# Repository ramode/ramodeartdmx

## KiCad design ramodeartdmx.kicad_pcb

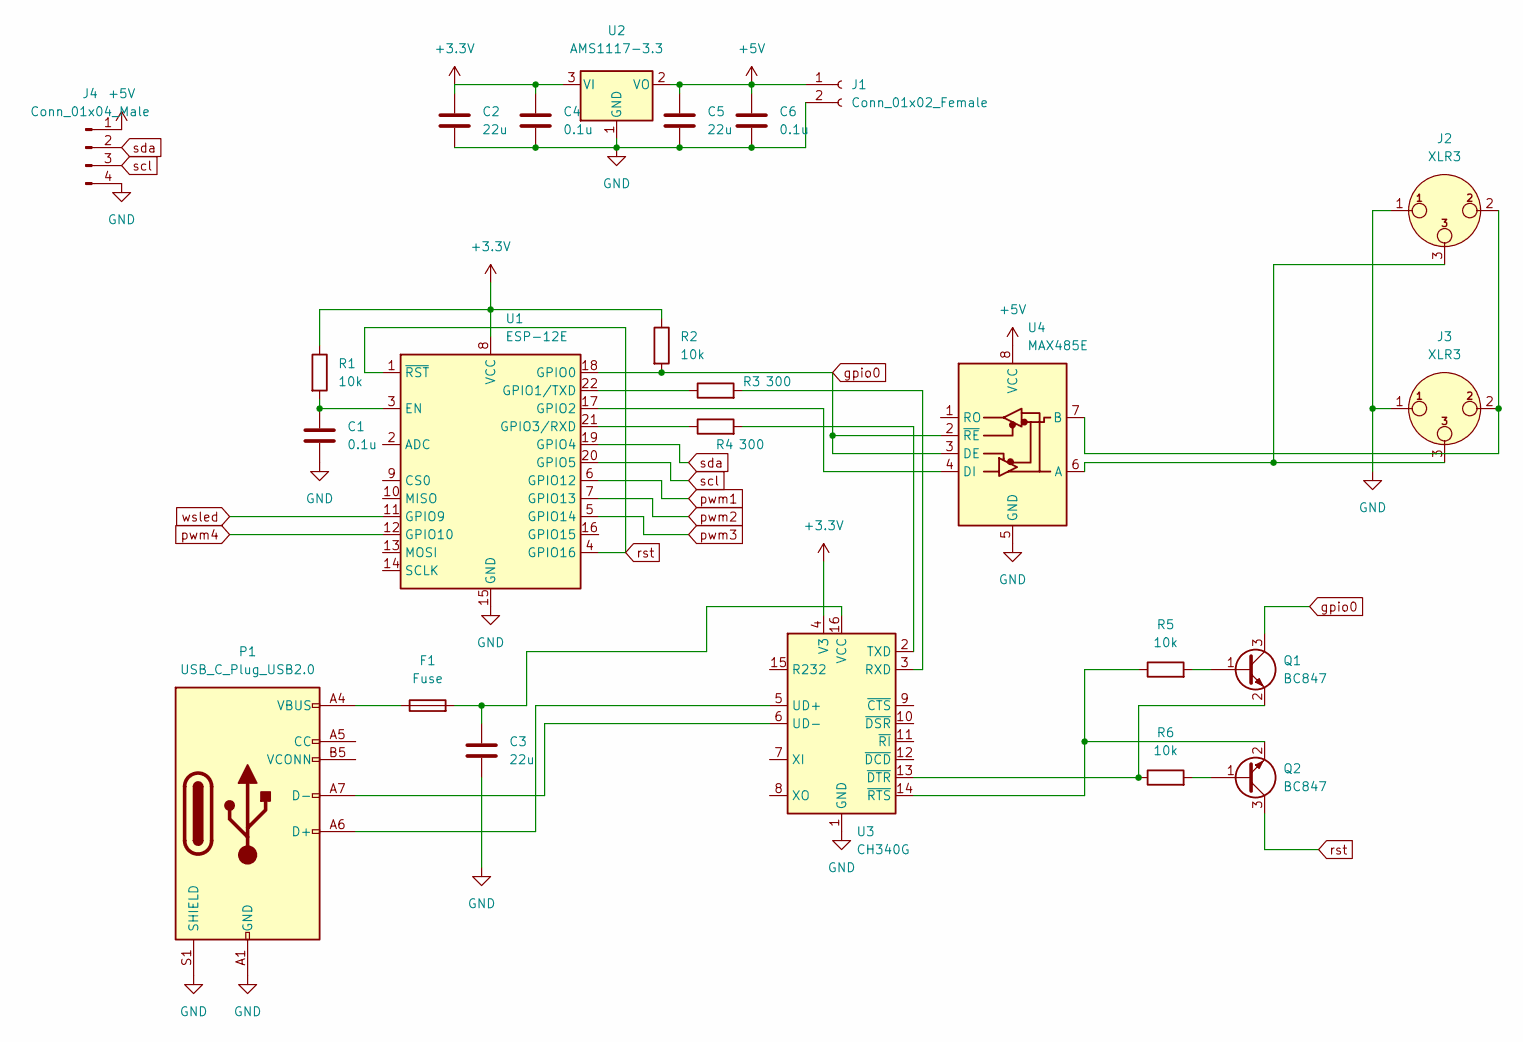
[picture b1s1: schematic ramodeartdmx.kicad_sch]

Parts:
C1, C4, C6: 0.1u; C_0805_2012Metric_Pad1.18x1.45mm_HandSolder
C2, C3, C5: 22u; C_0805_2012Metric_Pad1.18x1.45mm_HandSolder
F1: Fuse; Fuse_1206_3216Metric_Pad1.42x1.75mm_HandSolder
J1: Conn_01x02_Female; BarrelJack_Horizontal
J2, J3: XLR3; PinHeader_1x03_P2.54mm_Vertical
J4: Conn_01x04_Male; PinHeader_1x04_P2.54mm_Vertical
P1: USB_C_Plug_USB2.0; USB_C_Receptacle_JAE_DX07S016JA1R1500
Q1, Q2: BC847; SOT-23
R1, R2, R5, R6: 10k; R_0805_2012Metric_Pad1.20x1.40mm_HandSolder
R3, R4: 300; R_0805_2012Metric_Pad1.20x1.40mm_HandSolder
U1: ESP-12E
U2: AMS1117-3.3; SOT-223-3_TabPin2
U3: CH340G; SOIC-16_3.9x9.9mm_P1.27mm
U4: MAX485E; MSOP-8_3x3mm_P0.65mm

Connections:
+3V3: C2.1, C4.1, R1.1, R2.1, U1.8 (VCC), U2.3 (VI), U3.4 (V3)
+5V: C5.1, C6.1, J1.1, J4.1, U2.2 (VO), U4.8 (VCC)
GND: C1.2, C2.2, C3.2, C4.2, C5.2, C6.2, J1.2, J2.1, J3.1, J4.4, P1.A1 (GND), P1.A12 (GND), P1.B1 (GND), P1.B12 (GND), P1.S1 (SHIELD), U1.15 (GND), U2.1 (GND), U3.1 (GND), U4.5 (GND)
unnamed: C1.1, R1.2, U1.3 (EN)
unnamed: C3.1, F1.2, U3.16 (VCC)
unnamed: F1.1, P1.A4 (VBUS), P1.A9 (VBUS), P1.B4 (VBUS), P1.B9 (VBUS)
unnamed: J2.2, J3.2, U4.7 (B)
unnamed: J2.3, J3.3, U4.6 (A)
unnamed: P1.A6 (D+), U3.5 (UD+)
unnamed: P1.A7 (D-), U3.6 (UD-)
unnamed: Q1.1 (B), R5.2
unnamed: Q1.2 (E), R6.1, U3.13 (~DTR)
unnamed: Q2.1 (B), R6.2
unnamed: Q2.2 (E), R5.1, U3.14 (~RTS)
unnamed: R3.1, U1.22 (GPIO1/TXD)
unnamed: R3.2, U3.3 (RXD)
unnamed: R4.1, U1.21 (GPIO3/RXD)
unnamed: R4.2, U3.2 (TXD)
unnamed: U1.17 (GPIO2), U4.4 (DI)
gpio0: Q1.3 (C), R2.2, U1.18 (GPIO0), U4.2 (~RE), U4.3 (DE)
pwm1: U1.6 (GPIO12)
pwm2: U1.7 (GPIO13)
pwm3: U1.5 (GPIO14)
pwm4: U1.12 (GPIO10)
rst: Q2.3 (C), U1.1 (~RST), U1.4 (GPIO16)
scl: J4.3, U1.20 (GPIO5)
sda: J4.2, U1.19 (GPIO4)
wsled: U1.11 (GPIO9)

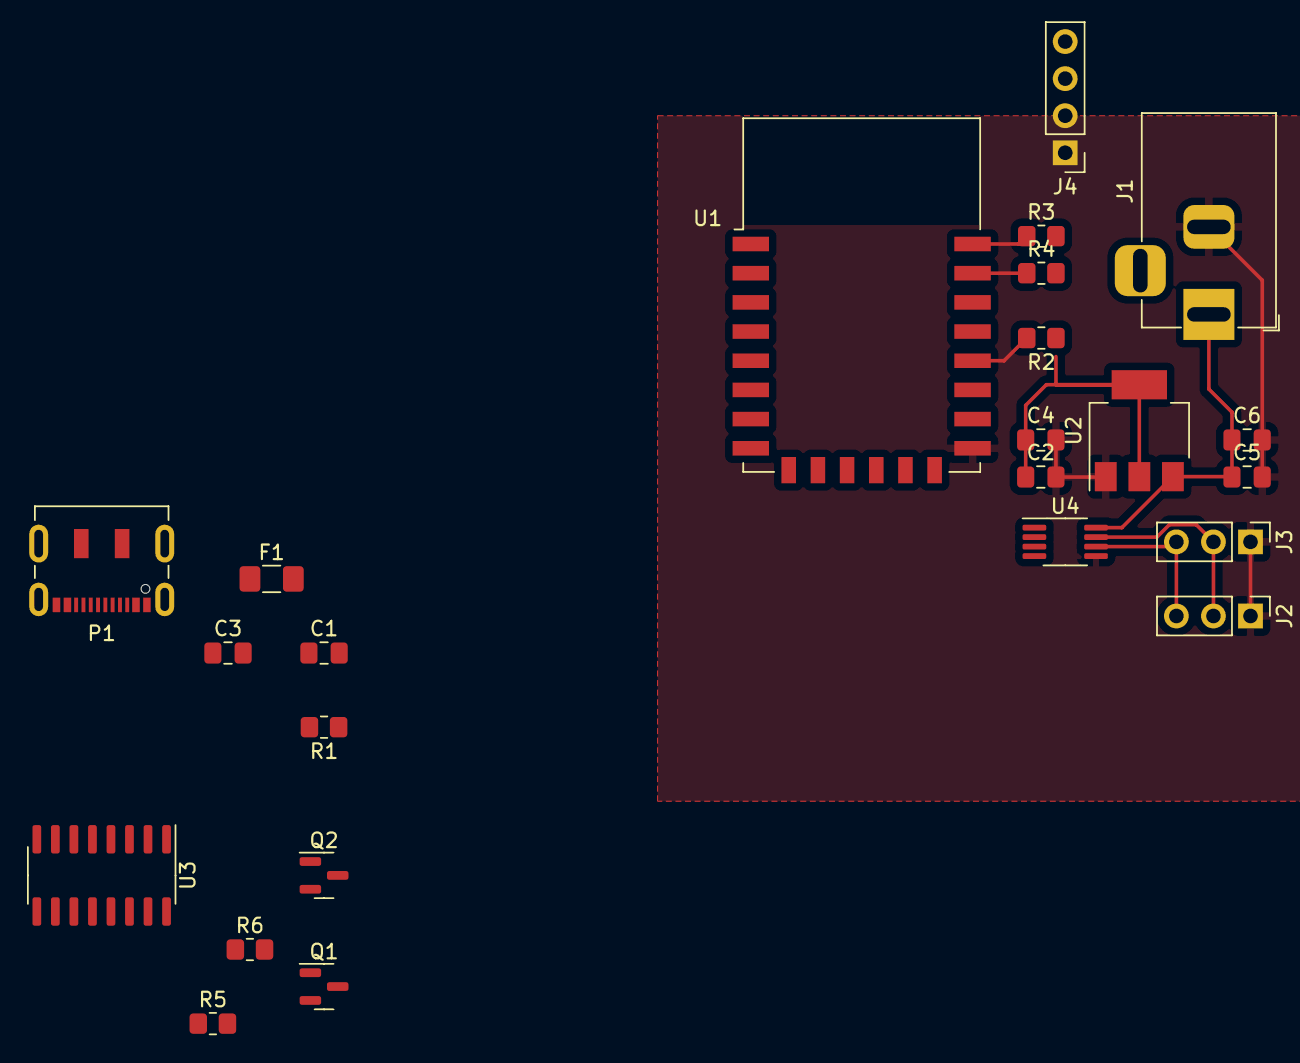
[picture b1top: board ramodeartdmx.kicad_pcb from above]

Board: 2 copper layers, 24 parts (0 on the bottom side), 23 nets.

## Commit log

2023-05-15 (120*80/4)
